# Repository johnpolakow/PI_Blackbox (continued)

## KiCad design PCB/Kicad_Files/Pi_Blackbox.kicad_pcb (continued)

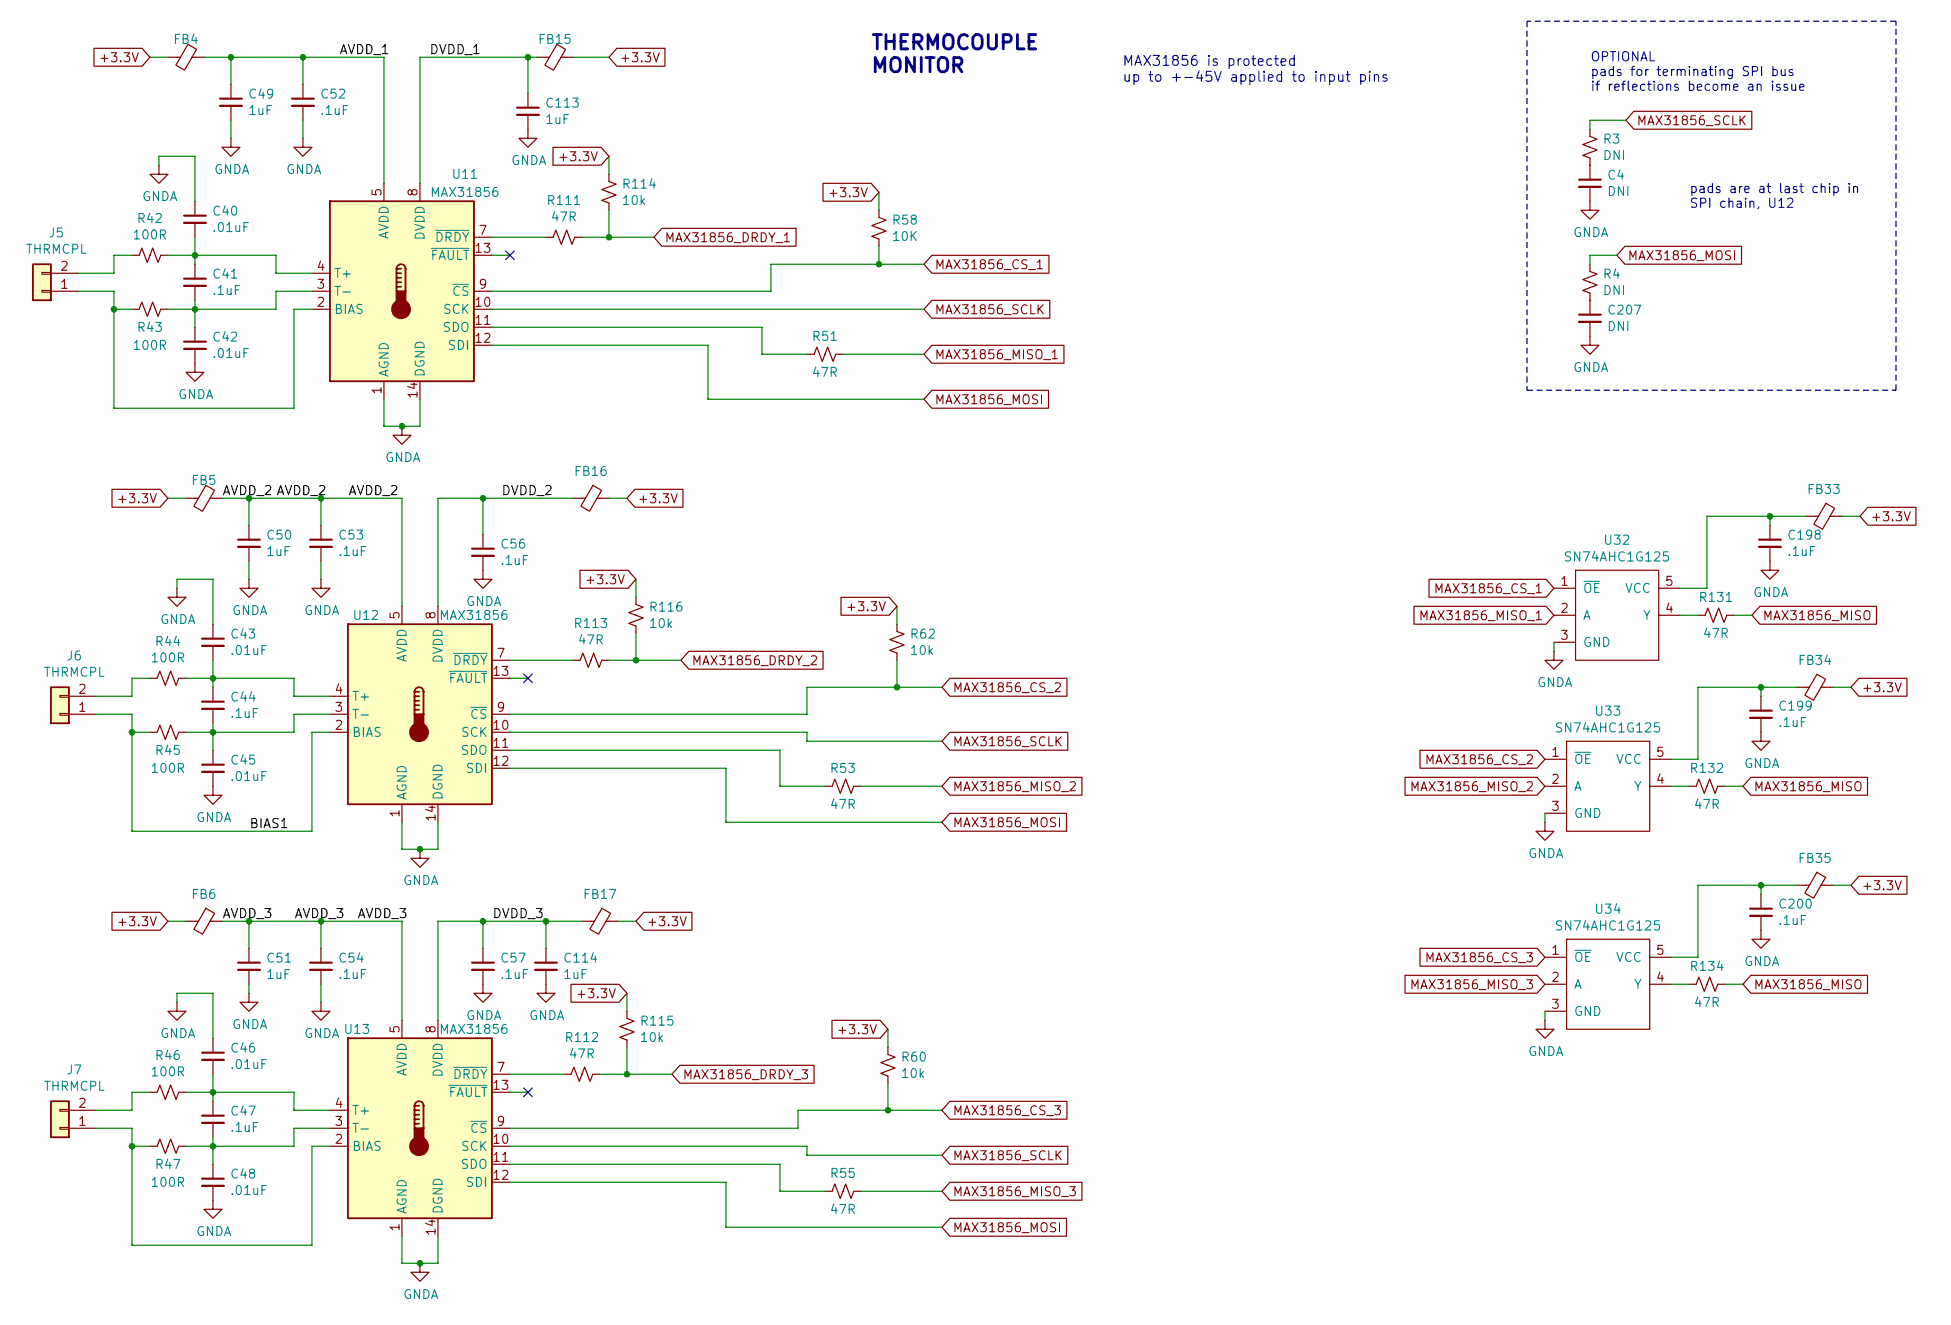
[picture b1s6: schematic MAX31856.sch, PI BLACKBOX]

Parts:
C4, C207: DNI; C_0603_1608Metric_Pad1.05x0.95mm_HandSolder
C40, C42, C43, C45, C46, C48: .01uF; C_0402_1005Metric
C41, C52, C53, C54, C56, C57: .1uF; C_0603_1608Metric_Pad1.05x0.95mm_HandSolder
C44, C47, C198, C199, C200: .1uF; C_0402_1005Metric
C49, C50, C51, C113, C114: 1uF; C_0603_1608Metric_Pad1.05x0.95mm_HandSolder
FB4, FB5, FB6, FB15, FB16, FB17: FB; R_0805_2012Metric_Pad1.15x1.40mm_HandSolder
FB33, FB34, FB35: FB; R_0402_1005Metric
J5, J6, J7: THRMCPL; Thermocouple_Connect
R3, R4: DNI; R_0603_1608Metric_Pad1.05x0.95mm_HandSolder
R42, R43, R44, R45, R46, R47: 100R; R_0402_1005Metric
R51, R53, R55, R111, R112, R113, R131, R132, R134: 47R; R_0402_1005Metric
R58: 10K; R_0402_1005Metric
R60, R62, R114, R115, R116: 10k; R_0402_1005Metric
U11, U12, U13: MAX31856; TSSOP-14_4.4x5mm_P0.65mm
U32, U33, U34: SN74AHC1G125; SOT-23-5_HandSoldering

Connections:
+3.3V: FB4.2, FB5.2, FB6.2, FB15.1, FB16.1, FB17.1, FB33.1, FB34.1, FB35.1, R58.1, R60.1, R62.1, R114.1, R115.1, R116.1; also elsewhere on the board
/MAX31856/AVDD_1: C49.1, C52.1, FB4.1, U11.5 (AVDD)
/MAX31856/AVDD_2: C50.1, C53.1, FB5.1, U12.5 (AVDD)
/MAX31856/AVDD_3: C51.1, C54.1, FB6.1, U13.5 (AVDD)
/MAX31856/BIAS1: J6.1, R45.2, U12.2 (BIAS)
/MAX31856/DVDD_1: C113.1, FB15.2, U11.8 (DVDD)
/MAX31856/DVDD_2: C56.1, FB16.2, U12.8 (DVDD)
/MAX31856/DVDD_3: C57.1, C114.1, FB17.2, U13.8 (DVDD)
DAC_MOSI: R4.1, U11.12 (SDI), U12.12 (SDI), U13.12 (SDI); also elsewhere on the board
DAC_SCLK: R3.1, U11.10 (SCK), U12.10 (SCK), U13.10 (SCK); also elsewhere on the board
GNDA: C4.2, C40.1, C42.2, C43.1, C45.2, C46.1, C48.2, C49.2, C50.2, C51.2, C52.2, C53.2, C54.2, C56.2, C57.2, C113.2, C114.2, C198.2, C199.2, C200.2, C207.2, U11.1 (AGND), U11.14 (DGND), U12.1 (AGND), U12.14 (DGND), U13.1 (AGND), U13.14 (DGND), U32.3 (GND), U33.3 (GND), U34.3 (GND); also elsewhere on the board
MAX31856_CS_1: R58.2, U11.9 (~CS), U32.1 (~OE); also elsewhere on the board
MAX31856_CS_2: R62.2, U12.9 (~CS), U33.1 (~OE); also elsewhere on the board
MAX31856_CS_3: R60.2, U13.9 (~CS), U34.1 (~OE); also elsewhere on the board
MAX31856_DRDY_1: R111.1, R114.2; also elsewhere on the board
MAX31856_DRDY_2: R113.1, R116.2; also elsewhere on the board
MAX31856_DRDY_3: R112.1, R115.2; also elsewhere on the board
MAX31856_MISO: R131.1, R132.1, R134.1; also elsewhere on the board
MAX31856_MISO_1: R51.1, U32.2 (A)
MAX31856_MISO_2: R53.1, U33.2 (A)
MAX31856_MISO_3: R55.1, U34.2 (A)
unnamed: C4.1, R3.2
unnamed: C40.2, C41.1, R42.1, U11.4 (T+)
unnamed: C41.2, C42.1, R43.1, U11.3 (T-)
unnamed: C43.2, C44.1, R44.1, U12.4 (T+)
unnamed: C44.2, C45.1, R45.1, U12.3 (T-)
unnamed: C46.2, C47.1, R46.1, U13.4 (T+)
unnamed: C47.2, C48.1, R47.1, U13.3 (T-)
unnamed: C198.1, FB33.2, U32.5 (VCC)
unnamed: C199.1, FB34.2, U33.5 (VCC)
unnamed: C200.1, FB35.2, U34.5 (VCC)
unnamed: C207.1, R4.2
unnamed: J5.1, R43.2, U11.2 (BIAS)
unnamed: J5.2, R42.2
unnamed: J6.2, R44.2
unnamed: J7.1, R47.2, U13.2 (BIAS)
unnamed: J7.2, R46.2
unnamed: R51.2, U11.11 (SDO)
unnamed: R53.2, U12.11 (SDO)
unnamed: R55.2, U13.11 (SDO)
unnamed: R111.2, U11.7 (~DRDY)
unnamed: R112.2, U13.7 (~DRDY)
unnamed: R113.2, U12.7 (~DRDY)
unnamed: R131.2, U32.4 (Y)
unnamed: R132.2, U33.4 (Y)
unnamed: R134.2, U34.4 (Y)

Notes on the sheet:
MAX31856 is protected up to +-45V applied to input pins
THERMOCOUPLE MONITOR
OPTIONAL pads for terminating SPI bus if reflections become an issue
pads are at last chip in SPI chain, U12

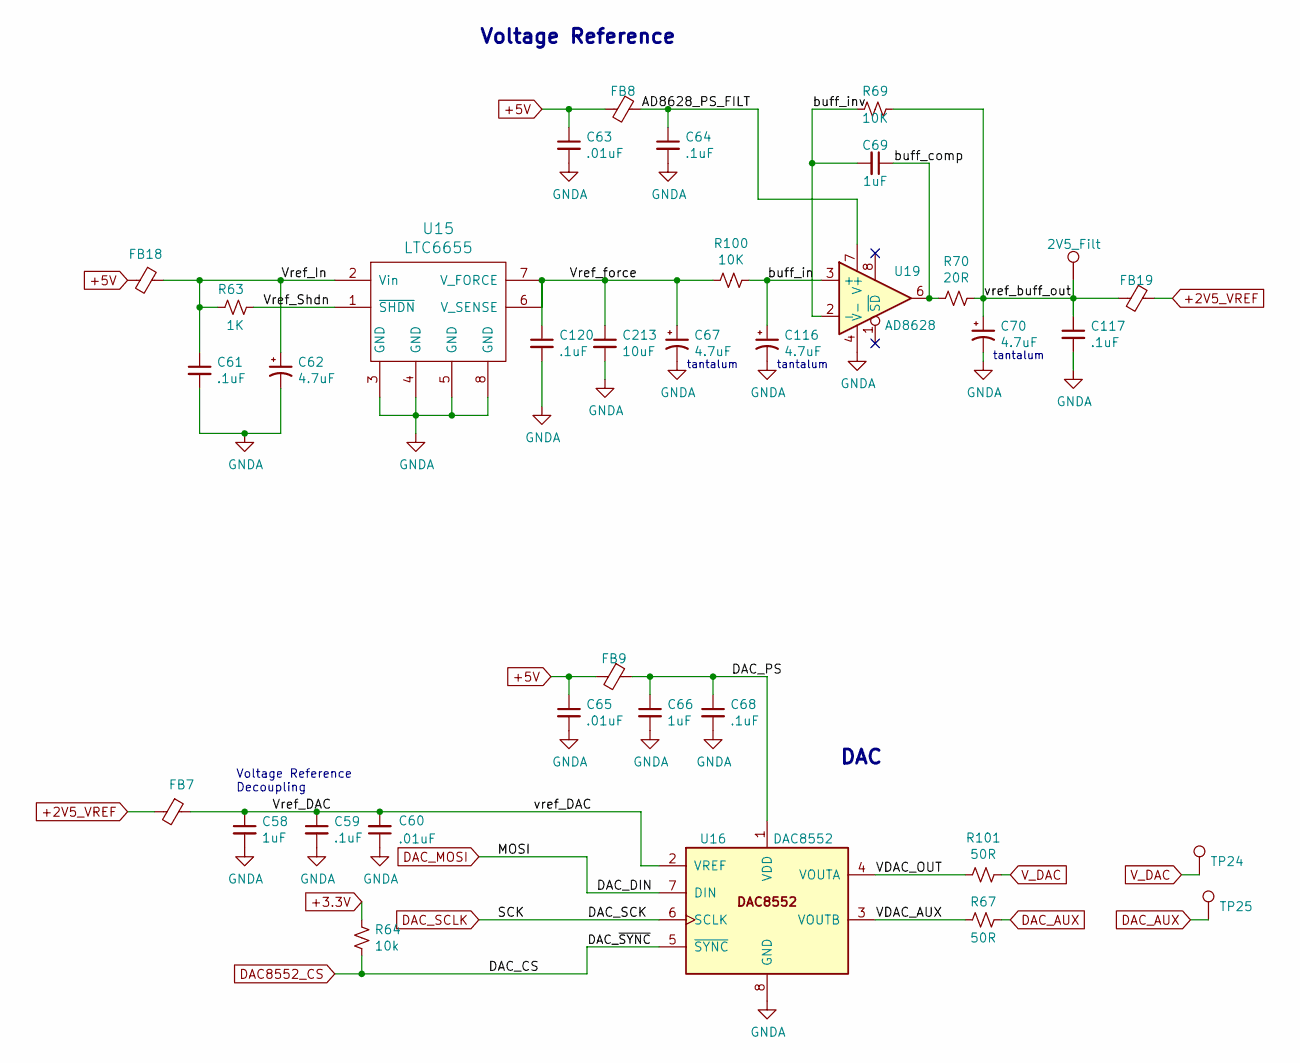
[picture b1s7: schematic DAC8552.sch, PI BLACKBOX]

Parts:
C58, C66, C69: 1uF; C_0805_2012Metric_Pad1.15x1.40mm_HandSolder
C59, C61, C64, C68, C117, C120: .1uF; C_0603_1608Metric_Pad1.05x0.95mm_HandSolder
C60, C63, C65: .01uF; C_0603_1608Metric_Pad1.05x0.95mm_HandSolder
C62, C67, C70, C116: 4.7uF; CP_EIA-3528-21_Kemet-B_Pad1.50x2.35mm_HandSolder
C213: 10uF; C_0805_2012Metric_Pad1.15x1.40mm_HandSolder
FB7, FB8, FB9, FB19: FB; R_0805_2012Metric_Pad1.15x1.40mm_HandSolder
FB18: FB; L_0805_2012Metric_Pad1.15x1.40mm_HandSolder
R63: 1K; R_0402_1005Metric
R64: 10k; R_0402_1005Metric
R67, R101: 50R; R_0402_1005Metric
R69: 10K; R_0603_1608Metric_Pad1.05x0.95mm_HandSolder
R70: 20R; R_0805_2012Metric_Pad1.15x1.40mm_HandSolder
R100: 10K; R_0402_1005Metric
TP23: 2V5_Filt; TestPoint_SMT_Keystone_5190
TP24: VDAC; TestPoint_SMT_Keystone_5190
TP25: DAC_AUX; TestPoint_Pad_D1.5mm
U15: LTC6655; LTC6655_LS8
U16: DAC8552; VSSOP-8_3.0x3.0mm_P0.65mm
U19: AD8628; SOIC-8_5.275x5.275mm_P1.27mm

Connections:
+2V5_VREF: FB7.2, FB19.1; also elsewhere on the board
+3.3V: R64.1; also elsewhere on the board
+5V: C63.1, C65.1, FB8.2, FB9.2, FB18.2; also elsewhere on the board
/DAC8552/AD8628_PS_FILT: C64.1, FB8.1, U19.7 (V+)
/DAC8552/DAC_PS: C66.1, C68.1, FB9.1, U16.1 (VDD)
/DAC8552/VDAC_AUX: R67.2, U16.3 (VOUTB)
/DAC8552/VDAC_OUT: R101.2, U16.4 (VOUTA)
/DAC8552/Vref_DAC: C58.1, C59.1, C60.2, FB7.1, U16.2 (VREF)
/DAC8552/Vref_In: C61.1, C62.1, FB18.1, R63.1, U15.2 (Vin)
/DAC8552/Vref_Shdn: R63.2, U15.1 (~SHDN)
/DAC8552/Vref_force: C67.1, C120.1, C213.1, R100.2, U15.6 (V_SENSE), U15.7 (V_FORCE)
/DAC8552/buff_comp: C69.1, R70.2, U19.6
/DAC8552/buff_in: C116.1, R100.1, U19.3 (+)
/DAC8552/buff_inv: C69.2, R69.2, U19.2 (-)
/DAC8552/vref_buff_out: C70.1, C117.1, FB19.2, R69.1, R70.1, TP23.1
DAC8552_CS: R64.2, U16.5 (~SYNC); also elsewhere on the board
DAC_AUX: R67.1, TP25.1
DAC_MOSI: U16.7 (DIN); also elsewhere on the board
DAC_SCLK: U16.6 (SCLK); also elsewhere on the board
GNDA: C58.2, C59.2, C60.1, C61.2, C62.2, C63.2, C64.2, C65.2, C66.2, C67.2, C68.2, C70.2, C116.2, C117.2, C120.2, C213.2, U15.3 (GND), U15.4 (GND), U15.5 (GND), U15.8 (GND), U16.8 (GND), U19.4 (V-); also elsewhere on the board
V_DAC: R101.1, TP24.1; also elsewhere on the board

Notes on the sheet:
Voltage Reference
DAC
Voltage Reference Decoupling
tantalum

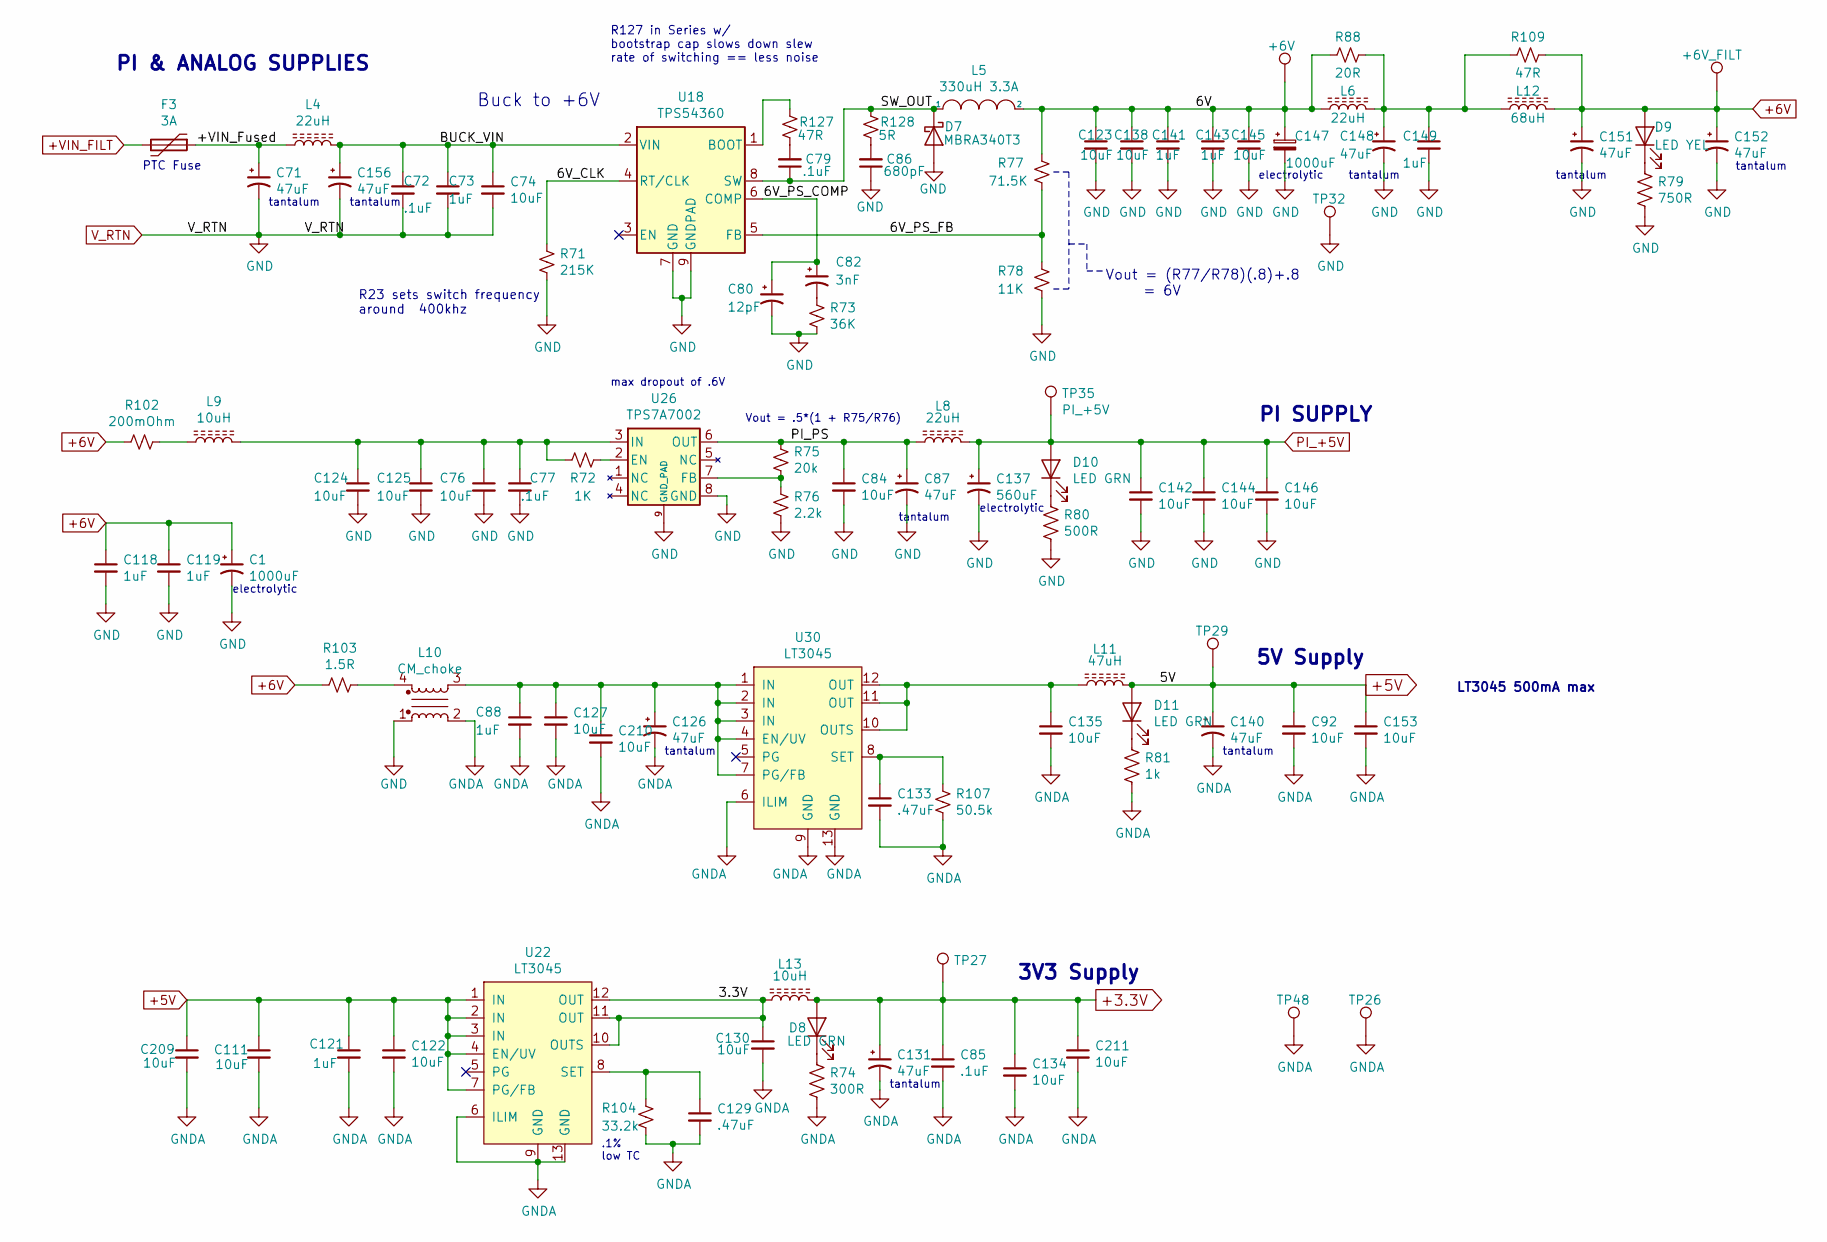
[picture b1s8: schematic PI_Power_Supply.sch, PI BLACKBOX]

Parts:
C1: 1000uF; CP_Radial_D12.5mm_P5.00mm; MFG Part # EEU-FR1V102B
C71, C87, C126, C131, C140, C148, C151, C152, C156: 47uF; T495X476K035ATE300
C72, C77: .1uF; C_0603_1608Metric_Pad1.05x0.95mm_HandSolder
C73, C88, C118, C119, C141, C143, C149: 1uF; C_0805_2012Metric_Pad1.15x1.40mm_HandSolder
C74, C76, C84, C92, C123, C124, C125, C127, C130, C134, C135, C138, C142, C144, C145, C146, C153: 10uF; C_1206_3216Metric_Pad1.42x1.75mm_HandSolder
C79: .1uF; C_0805_2012Metric_Pad1.15x1.40mm_HandSolder
C80: 12pF; C_0603_1608Metric_Pad1.05x0.95mm_HandSolder
C82: 3nF; C_0603_1608Metric_Pad1.05x0.95mm_HandSolder
C85: .1uF; R_0603_1608Metric_Pad1.05x0.95mm_HandSolder
C86: 680pF; C_0603_1608Metric_Pad1.05x0.95mm_HandSolder
C111, C122, C209, C210, C211: 10uF; C_0805_2012Metric_Pad1.15x1.40mm_HandSolder
C121: 1uF; C_0603_1608Metric_Pad1.05x0.95mm_HandSolder
C129, C133: .47uF; C_0402_1005Metric
C137: 560uF; CP_Radial_D10.0mm_P5.00mm
C147: 1000uF; CP_Radial_D12.5mm_P5.00mm
D7: MBRA340T3; MBRA430T
D8, D10, D11: LED GRN; LED_0805_2012Metric_Pad1.15x1.40mm_HandSolder
D9: LED YEL; LED_0805_2012Metric_Pad1.15x1.40mm_HandSolder
F3: 3A; Fuse_2920
L4: 22uH; L_Bourns_SRP1038
L5: 330uH 3.3A; Murata1433433C
L6, L8: 22uH; Sumida_CDRH105
L9: 10uH; 10uH_Wurth_74479887310A
L10: CM_choke; CM_Choke_EPCOS_B82720K
L11: 47uH; RLB9012-470KL
L12: 68uH; L_Wuerth_WE-PD
L13: 10uH; L_1210_3225Metric_Pad1.42x2.65mm_HandSolder
R71: 215K; R_0603_1608Metric_Pad1.05x0.95mm_HandSolder
R72: 1K; R_0402_1005Metric
R73: 36K; R_0603_1608Metric_Pad1.05x0.95mm_HandSolder
R74: 300R; R_0402_1005Metric
R75: 20k; R_0603_1608Metric_Pad1.05x0.95mm_HandSolder
R76: 2.2k; R_0603_1608Metric_Pad1.05x0.95mm_HandSolder
R77: 71.5K; R_0603_1608Metric_Pad1.05x0.95mm_HandSolder
R78: 11K; R_0603_1608Metric_Pad1.05x0.95mm_HandSolder
R79: 750R; R_0402_1005Metric
R80: 500R; R_0402_1005Metric
R81: 1k; R_0402_1005Metric
R88: 20R; R_1210_3225Metric_Pad1.42x2.65mm_HandSolder
R102: 200mOhm; R_1206_3216Metric_Pad1.42x1.75mm_HandSolder
R103: 1.5R; R_1206_3216Metric_Pad1.42x1.75mm_HandSolder
R104: 33.2k; R_0402_1005Metric
R107: 50.5k; R_0603_1608Metric_Pad1.05x0.95mm_HandSolder
R109: 47R; R_1210_3225Metric_Pad1.42x2.65mm_HandSolder
R127: 47R; R_0603_1608Metric_Pad1.05x0.95mm_HandSolder
R128: 5R; R_0805_2012Metric_Pad1.15x1.40mm_HandSolder
TP16: +6V_FILT; TestPoint_SMT_Keystone_5190
TP26, TP48: GNDA; TestPoint_SMT_Keystone_5190
TP27: +3V3; TestPoint_SMT_Keystone_5190
TP28: +6V; TestPoint_SMT_Keystone_5190
TP29: +5V_FILT; TestPoint_SMT_Keystone_5190
TP32: GND; TestPoint_SMT_Keystone_5190
TP35: PI_+5V; TestPoint_SMT_Keystone_5190
U18: TPS54360; Power_Pad_SO
U22, U30: LT3045; MSOP-12-1EP_3x4mm_P0.65mm_EP1.65x2.85mm_ThermalVias
U26: TPS7A7002; SOIC-8-1EP_3.9x4.9mm_P1.27mm_EP2.514x3.2mm_ThermalVias

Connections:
+3.3V: C85.1, C131.1, C134.1, C211.1, D8.2 (A), L13.2, TP27.1; also elsewhere on the board
+5V: C92.1, C111.1, C121.1, C122.1, C140.1, C153.1, C209.1, D11.2 (A), L11.2, TP29.1, U22.1 (IN), U22.2 (IN), U22.3 (IN), U22.4 (EN/UV), U22.7 (PG/FB); also elsewhere on the board
+6V: C1.1, C118.1, C119.1, C151.1, C152.1, D9.2 (A), L12.2, R102.2, R103.2, R109.1, TP16.1; also elsewhere on the board
+VIN_FILT: F3.2; also elsewhere on the board
/PI_Power_Supply/3.3V: C130.1, L13.1, U22.10 (OUTS), U22.11 (OUT), U22.12 (OUT)
/PI_Power_Supply/6V: C123.1, C138.1, C141.1, C143.1, C145.1, C147.1, L5.2, L6.1, R77.1, R88.2, TP28.1
/PI_Power_Supply/6V_CLK: R71.1, U18.4 (RT/CLK)
/PI_Power_Supply/6V_PS_COMP: C80.1, C82.1, U18.6 (COMP)
/PI_Power_Supply/6V_PS_FB: R77.2, R78.1, U18.5 (FB)
/PI_Power_Supply/+VIN_Fused: C71.1, F3.1, L4.1
/PI_Power_Supply/BUCK_VIN: C72.1, C73.1, C74.1, C156.1, L4.2, U18.2 (VIN)
/PI_Power_Supply/PI_PS: C84.1, C87.1, L8.1, R75.1, U26.6 (OUT)
/PI_Power_Supply/SW_OUT: C79.1, D7.1 (K), L5.1, R128.1, U18.8 (SW)
GND: C1.2, C71.2, C72.2, C73.2, C74.2, C76.2, C77.2, C80.2, C84.2, C86.1, C87.2, C118.2, C119.2, C123.2, C124.2, C125.2, C137.2, C138.2, C141.2, C142.2, C143.2, C144.2, C145.2, C146.2, C147.2, C148.2, C149.2, C151.2, C152.2, C156.2, D7.2 (A), L10.1, R71.2, R73.2, R76.2, R78.2, R79.2, R80.2, TP32.1, U18.7 (GND), U18.9 (GNDPAD), U26.8 (GND), U26.9 (GND_PAD); also elsewhere on the board
GNDA: C85.2, C88.2, C92.2, C111.2, C121.2, C122.2, C126.2, C127.2, C129.2, C130.2, C131.2, C133.2, C134.2, C135.2, C140.2, C153.2, C209.2, C210.2, C211.2, L10.2, R74.2, R81.2, R104.2, R107.2, TP26.1, TP48.1, U22.6 (ILIM), U22.9 (GND), U22.13 (GND), U30.6 (ILIM), U30.9 (GND), U30.13 (GND); also elsewhere on the board
unnamed: C79.2, R127.2
unnamed: C82.2, R73.1
unnamed: C86.2, R128.2
unnamed: C76.1, C77.1, C124.1, C125.1, L9.2, R72.2, U26.3 (IN)
unnamed: C88.1, C126.1, C127.1, C210.1, L10.3, U30.1 (IN), U30.2 (IN), U30.3 (IN), U30.4 (EN/UV), U30.7 (PG/FB)
unnamed: C129.1, R104.1, U22.8 (SET)
unnamed: C133.1, R107.1, U30.8 (SET)
unnamed: C135.1, L11.1, U30.10 (OUTS), U30.11 (OUT), U30.12 (OUT)
unnamed: C148.1, C149.1, L6.2, L12.1, R88.1, R109.2
unnamed: D8.1 (K), R74.1
unnamed: D9.1 (K), R79.1
unnamed: D10.1 (K), R80.1
unnamed: D11.1 (K), R81.1
unnamed: L9.1, R102.1
unnamed: L10.4, R103.1
unnamed: R72.1, U26.2 (EN)
unnamed: R75.2, R76.1, U26.7 (FB)
unnamed: R127.1, U18.1 (BOOT)
PI_+5V: C137.1, C142.1, C144.1, C146.1, D10.2 (A), L8.2, TP35.1; also elsewhere on the board

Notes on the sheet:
Vout = (R77/R78)(.8)+.8 = 6V
R23 sets switch frequency around 400khz
3V3 Supply
Buck to +6V
PTC Fuse
PI & ANALOG SUPPLIES
Vout = .5*(1 + R75/R76)
PI SUPPLY
tantalum
max dropout of .6V
.1% low TC
electrolytic
R127 in Series w/ bootstrap cap slows down slew rate of switching == less noise
LT3045 500mA max
5V Supply

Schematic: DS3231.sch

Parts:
BT1: Battery_Holder; BatteryHolder_Keystone_1058_2032; MFG Part # 1058
C160, C168: 0.1uF; C_0603_1608Metric_Pad1.05x0.95mm_HandSolder
FB26: ferrite; R_0603_1608Metric_Pad1.05x0.95mm_HandSolder
R121, R122: 22R; R_0402_1005Metric
R123, R124: 2k; R_0402_1005Metric
R125, R126: 10k; R_0402_1005Metric
U29: DS3231MZ+; SOIC-8_W3.9mm; MPN DS3231MZ/V+; Digi-Key_PN DS3231MZ/V+-ND

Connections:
+3.3V: FB26.2, R123.1, R124.1, R125.1, R126.1; also elsewhere on the board
GNDA: BT1.2 (-), C160.2, C168.2, U29.5 (GND); also elsewhere on the board
unnamed: C160.1, FB26.1, U29.2 (VCC)
unnamed: R121.1, R124.2, U29.7 (SDA)
unnamed: R122.1, R123.2, U29.8 (SCL)
unnamed: R125.2, U29.3 (~INT~/SQW)
unnamed: R126.2, U29.1 (32KHZ)
PI_SCL: R122.2; also elsewhere on the board
PI_SDA: R121.2; also elsewhere on the board
VBat: BT1.1 (+), C168.1, U29.6 (VBAT); also elsewhere on the board

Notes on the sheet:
REAL TIME CLOCK DS3231

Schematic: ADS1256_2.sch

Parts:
C181: 4.7uF; CP_EIA-3528-21_Kemet-B_Pad1.50x2.35mm_HandSolder
C182, C184, C208: 1uF; C_0603_1608Metric_Pad1.05x0.95mm_HandSolder
C183, C186, C188, C190, C191: .1uF; C_0603_1608Metric_Pad1.05x0.95mm_HandSolder
C185: .1uF; C_0805_2012Metric_Pad1.15x1.40mm_HandSolder
C187, C189: 1uF; R_0603_1608Metric_Pad1.05x0.95mm_HandSolder
C192, C193: 20pF; C_0603_1608Metric_Pad1.05x0.95mm_HandSolder
L16, L17: 10uH; MLZ2012N100LT000
R130, R138: 2k; R_0402_1005Metric
R133: 10k; R_0402_1005Metric
R136, R137: 47R; R_0402_1005Metric
U31: ADS1256; SSOP-28_5.3x10.2mm_P0.65mm
Y2: 7.68 Mhz; Crystal_SMD_TXC

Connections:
+2V5_VREF: C181.1, C182.1, C183.1, U31.4 (VREFP); also elsewhere on the board
+3.3V: C184.1, L16.1, R130.1, R133.1, R138.1; also elsewhere on the board
+5V: C186.1, L17.1; also elsewhere on the board
/ADS1256_2/ADS2_AVDD: C188.1, C189.1, C191.1, L17.2, U31.1 (AVDD)
/ADS1256_2/ADS2_DRDY2: R136.2, U31.21 (~DRDY)
/ADS1256_2/ADS2_DVDD: C187.1, C190.1, L16.2, U31.16 (DVDD)
/ADS1256_2/ADS2_MISO2: R137.2, U31.22 (DOUT)
ADS1256_MISO: R137.1; also elsewhere on the board
ADS1256_MOSI: U31.23 (DIN); also elsewhere on the board
ADS1256_SCLK: U31.24 (SCLK); also elsewhere on the board
COOL_PWR_I: C208.1, U31.6 (AIN0); also elsewhere on the board
CRYSTALA: C192.1, U31.19 (XTAL1/CLKIN), Y2.2
CRYSTALB: C193.1, U31.18 (XTAL2), Y2.1
GNDA: C181.2, C182.2, C183.2, C184.2, C186.2, C187.2, C188.2, C189.2, C190.2, C191.2, C192.2, C193.2, C208.2, U31.2 (AGND), U31.3 (VREFN), U31.5 (AINCOM), U31.7 (AIN1), U31.11 (AIN5), U31.13 (AIN7), U31.17 (DGND); also elsewhere on the board
HEAT_LOAD_I: U31.10 (AIN4); also elsewhere on the board
HEAT_LOAD_V: U31.12 (AIN6); also elsewhere on the board
TEMP_DIODE: C185.1, U31.8 (AIN2); also elsewhere on the board
TEMP_DIODE_RTN: C185.2, U31.9 (AIN3); also elsewhere on the board
~ADS1256_CS_1: R130.2, U31.20 (~CS); also elsewhere on the board
~ADS1256_RESET: R133.2, U31.15 (~RESET); also elsewhere on the board
~ADS1265_DRDY2: R136.1, R138.2; also elsewhere on the board

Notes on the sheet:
ADC
Analog Inputs

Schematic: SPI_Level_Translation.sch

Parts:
C201, C202, C203, C204, C205, C206: 0.1uF; C_0603_1608Metric_Pad1.05x0.95mm_HandSolder
R5, R6, R7, R147: 10k; R_0402_1005Metric
R135, R139, R140, R141, R142, R143, R144, R145, R146: 47R; R_0402_1005Metric
TP5: MISO_1; TestPoint_SMT_Keystone_5190
TP7: MOSI_1; TestPoint_SMT_Keystone_5190
TP8: SCLK_0; TestPoint_SMT_Keystone_5190
TP9: SCLK_1; TestPoint_SMT_Keystone_5190
TP10: MOSI_0; TestPoint_SMT_Keystone_5190
TP11: GND; TestPoint_SMT_Keystone_5190
TP12: MISO_0; TestPoint_SMT_Keystone_5190
TP50: PI_SCLK_0; TestPoint_SMT_Keystone_5190
U35, U36, U37: SN74HC125; SN74LVC125APWR; MPN SN74HC125A; Digi-Key_PN 296-1222-1-ND

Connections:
+3.3V: C201.1, C202.1, C203.1, C204.1, C205.1, C206.1, R5.1, R6.1, R7.1, R147.1, U35.14 (VCC), U36.14 (VCC), U37.14 (VCC); also elsewhere on the board
ADS1256_MISO: TP12.1, U35.12 (4A); also elsewhere on the board
ADS1256_MOSI: R142.1, TP10.1; also elsewhere on the board
ADS1256_SCLK: R141.1, TP8.1; also elsewhere on the board
DAC_MOSI: R144.1, R146.1; also elsewhere on the board
DAC_SCLK: R143.1, R145.1; also elsewhere on the board
GND: C201.2, C202.2, C203.2, C204.2, C205.2, C206.2, TP11.1, U35.7 (GND), U36.7 (GND), U37.7 (GND); also elsewhere on the board
MAX31856_MISO: U36.12 (4A), U37.12 (4A); also elsewhere on the board
unnamed: R135.1, U35.11 (4Y)
unnamed: R139.1, U36.11 (4Y)
unnamed: R140.1, TP5.1, U37.11 (4Y)
unnamed: R141.2, U35.3 (1Y)
unnamed: R142.2, U35.6 (2Y)
unnamed: R143.2, U36.3 (1Y)
unnamed: R144.2, U36.6 (2Y)
unnamed: R145.2, U37.3 (1Y)
unnamed: R146.2, U37.6 (2Y)
PI_MISO_0: R135.2, R139.2; also elsewhere on the board
PI_MISO_1: R140.2; also elsewhere on the board
PI_MOSI_0: U35.5 (2A), U36.5 (2A); also elsewhere on the board
PI_MOSI_1: TP7.1, U37.5 (2A); also elsewhere on the board
PI_SCLK_0: TP50.1, U35.2 (1A), U36.2 (1A); also elsewhere on the board
PI_SCLK_1: TP9.1, U37.2 (1A); also elsewhere on the board
~BUF_EN_0: R7.2, R147.2, U35.1 (~1OE), U35.4 (~2OE), U35.13 (~4OE); also elsewhere on the board
~BUF_EN_1: R5.2, U36.1 (~1OE), U36.4 (~2OE), U36.13 (~4OE); also elsewhere on the board
~BUF_EN_2: R6.2, U37.1 (~1OE), U37.4 (~2OE), U37.13 (~4OE); also elsewhere on the board

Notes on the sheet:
turn on when ads1 or ads2 CS goes low

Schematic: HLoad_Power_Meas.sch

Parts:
C13: 1.5uF; C_1210_3225Metric_Pad1.42x2.65mm_HandSolder
C157, C158: 0.1uF; C_0603_1608Metric_Pad1.05x0.95mm_HandSolder
C161: 1uF; C_0603_1608Metric_Pad1.05x0.95mm_HandSolder
C162: .1uF; C_0402_1005Metric
C163, C164, C167: 1uF; C_1210_3225Metric_Pad1.42x2.65mm_HandSolder
C165: 10uF; C_0805_2012Metric_Pad1.15x1.40mm_HandSolder
C166: .1uF; C_0603_1608Metric_Pad1.05x0.95mm_HandSolder
FB11, FB21, FB22, FB23: FB; R_0603_1608Metric_Pad1.05x0.95mm_HandSolder
R15: 1 kΩ; R_0402_1005Metric
R16: 1KΩ; R_0402_1005Metric
R17: 100 Ω; R_0402_1005Metric
R18: 1KΩ; R_0603_1608Metric_Pad1.05x0.95mm_HandSolder
R83: 100 Ω; R_0603_1608Metric_Pad1.05x0.95mm_HandSolder
TP34, TP36: test_pad; Probe_Test_Pad
U4: AD8278; SOIC-8_5.23x5.23mm_P1.27mm
U5: LT5400; MSOP-8_3x3mm_P0.65mm
U25: AD8417; SOIC-8_3.9x4.9mm_P1.27mm
U27, U28: AD8628; SOIC-8_3.9x4.9mm_P1.27mm
VLoad/4, VLoad/8: Jumper; SolderJumper-2_P1.3mm_Open_RoundedPad1.0x1.5mm

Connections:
+5V: FB21.1, FB22.1, FB23.1; also elsewhere on the board
/Heat_Load/HLoad: U25.8 (IN+); also elsewhere on the board
/Heat_Load/HLoad_Power_Meas/GUARD: C165.2, R18.2, U28.2 (-)
/Heat_Load/HLoad_Power_Meas/GUARD2: C161.2, R16.2, U27.2 (-)
/Heat_Load/HLoad_Power_Meas/I_Load: R15.2, U25.5 (OUT)
/Heat_Load/HLoad_Power_Meas/VLoad_div2: U4.5, U4.6, U5.1 (R1_in)
/Heat_Load/HLoad_Power_Meas/V_div4: TP34.1, U5.2 (R2_in), U5.3 (R3_in), VLoad/4.1
/Heat_Load/HLoad_Power_Meas/V_div8: TP36.1, U5.5 (R4_out), U5.6 (R3_out), VLoad/8.1
GND: C13.1, U4.2, U4.4 (V-); also elsewhere on the board
GNDA: C157.2, C158.2, C162.2, C163.2, C164.2, C166.2, C167.2, U4.1, U5.4 (R4_in), U25.2 (GND), U25.3 (REF2), U25.7 (REF1), U27.4 (V-), U28.4 (V-); also elsewhere on the board
HEAT_LOAD_I: C164.1, R16.1, R17.1; also elsewhere on the board
HEAT_LOAD_P: C13.2, U4.3, U25.1 (IN-); also elsewhere on the board
HEAT_LOAD_V: C167.1, R18.1, R83.1; also elsewhere on the board
LOAD_PS: FB11.1; also elsewhere on the board
unnamed: C157.1, FB11.2, U4.7 (V+)
unnamed: C158.1, FB21.2, U25.6 (VS)
unnamed: C161.1, R17.2, U27.6
unnamed: C162.1, FB22.2, U27.7 (V+)
unnamed: C163.1, U28.3 (+), VLoad/4.2, VLoad/8.2
unnamed: C165.1, R83.2, U28.6
unnamed: C166.1, FB23.2, U28.7 (V+)
unnamed: R15.1, U27.3 (+)
unnamed: U5.7 (R2_out), U5.8 (R1_out)

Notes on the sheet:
FILM
AD8278 Difference Amp in divide by 2 config
LT5400 divides by 4
AD8417 has a Gain of 60
FILM
Total Division Ratio is 8. Max Input Voltage is around 17 V, so output is scaled to 2.125 VMax, which is within ADC reference voltage of 2.5V

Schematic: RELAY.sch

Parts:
C28: 560uF; CP_Radial_D10.0mm_P5.00mm
C95: 47uF; T495X476K035ATE300
C102: .1uF; C_0603_1608Metric_Pad1.05x0.95mm_HandSolder
C103, C112: 1uF; C_0805_2012Metric_Pad1.15x1.40mm_HandSolder
C110: 1000uF; CP_Radial_D12.5mm_P5.00mm
D1, D3: 1N5819; SOD123
D4: 1N4148; SOD123
D12: 1N4148W; SOD123
D13: LED GRN; LED_0805_2012Metric_Pad1.15x1.40mm_HandSolder
D15: LED GREEN; LED_0805_2012Metric_Pad1.15x1.40mm_HandSolder
D17: LED RED; LED_0805_2012Metric_Pad1.15x1.40mm_HandSolder
JP1, JP2, JP3, JP4: Jumper_NO; SolderJumper-2_P1.3mm_Open_RoundedPad1.0x1.5mm
K1: DSP1-L2-DC5V; Panasonic_DSP1-L2-DC5V-F
Q3: BCM856DS; SOT-23-6_Handsoldering
Q4, Q7: MMBT2222A; SOT-23_Handsoldering
Q5: DMG6602
Q6: IRML6401; SOT-23_Handsoldering
R30, R32, R33: 50KΩ; R_0603_1608Metric_Pad1.05x0.95mm_HandSolder
R82: 750Ω; R_0603_1608Metric_Pad1.05x0.95mm_HandSolder
R85, R86: 500Ω; R_0402_1005Metric
R87, R98, R99: 1KΩ; R_0402_1005Metric
R96, R97: 47KΩ; R_0603_1608Metric_Pad1.05x0.95mm_HandSolder

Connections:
+5V: Q3.1 (E), Q6.3 (D); also elsewhere on the board
+5V_RELAY_PS: C110.1, D4.1 (K), D12.1 (K), D15.2 (A), K1.1, K1.2, Q3.4 (E), Q6.2 (S)
+12V_REG: D1.2 (A), K1.8, K1.9, R30.1, R32.1; also elsewhere on the board
/Power_Input/Power_Measure/RELAY_ON: C95.1, C102.1, C103.1, D13.2 (A), K1.5; also elsewhere on the board
/Power_Input/RELAY/COOLER_OFF: C112.1, D17.2 (A), K1.12
COIL_A: D4.2 (A), JP1.1, JP1.2, JP2.1, JP3.1, K1.16, Q4.3 (C)
COIL_B: D12.2 (A), JP2.2, JP3.2, JP4.1, JP4.2, K1.15, Q7.3 (C)
GND: C95.2, C102.2, C103.2, C112.2, R87.2, R99.2; also elsewhere on the board
GNDA: C28.2, C110.2, Q4.2 (E), Q5.5 (S), Q7.2 (E), R33.2, R96.2, R97.2, R98.2; also elsewhere on the board
unnamed: C28.1, D1.1 (K), Q5.2 (S), R30.2
unnamed: D3.1 (K), R82.2
unnamed: D3.2 (A), Q5.1 (G), Q5.4 (D), R33.1
unnamed: D13.1 (K), R87.1
unnamed: D15.1 (K), R98.1
unnamed: D17.1 (K), R99.1
unnamed: Q3.2 (B), Q3.5 (B), Q3.6 (C), R96.1
unnamed: Q3.3 (C), Q6.1 (G), R97.1
unnamed: Q4.1 (B), R82.1, R85.2
unnamed: Q5.3 (G), Q5.6 (D), R32.2
unnamed: Q7.1 (B), R86.1
RELAY_RESET: R86.2; also elsewhere on the board
RELAY_SET: R85.1; also elsewhere on the board

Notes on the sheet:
nominal coil current is 60 mA
RELAY_OFF
Automatically shuts off relay at power off
Supply for relay reset circuit
IDEAL DIODE (SUPPLY TO TURN OFF RELAY)
RELAY_ON
RELAY OFF INDICATOR
ON INDICATOR

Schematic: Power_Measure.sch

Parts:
C99, C115: .1uF; C_0603_1608Metric_Pad1.05x0.95mm_HandSolder
C100, C101, C107, C214: 10uF; C_1206_3216Metric_Pad1.42x1.75mm_HandSolder
C128, C174, C175, C176, C179: 1uF; C_0805_2012Metric_Pad1.15x1.40mm_HandSolder
C136: 47uF; T495X476K035ATE300
C139, C150: 100uF; C_1210_3225Metric_Pad1.42x2.65mm_HandSolder
C169: 3.3uF; C_Rect_L7.2mm_W5.5mm_P5.00mm_FKS2_FKP2_MKS2_MKP2
C170: 1uF; C_1210_3225Metric_Pad1.42x2.65mm_HandSolder
C171, C172, C173: 0.1uF; C_0603_1608Metric_Pad1.05x0.95mm_HandSolder
C177: 1000pF; C_0402_1005Metric
C180: 4.7uF; CP_EIA-3528-21_Kemet-B_Pad1.50x2.35mm_HandSolder
D5: LED_GRN; LED_0805_2012Metric_Pad1.15x1.40mm_HandSolder
FB24: FB; R_0805_2012Metric_Pad1.15x1.40mm_HandSolder
FB25, FB28: Ferrite; R_0805_2012Metric_Pad1.15x1.40mm_HandSolder
FB30: ferrite; R_0805_2012Metric_Pad1.15x1.40mm_HandSolder
FB31: FB; L_0603_1608Metric_Pad1.05x0.95mm_HandSolder
FB32: ferrite; L_1210_3225Metric_Pad1.42x2.65mm_HandSolder
R20: 500; R_0603_1608Metric_Pad1.05x0.95mm_HandSolder
R94: 56 mΩ; R_1206_3216Metric_Pad1.42x1.75mm_HandSolder
R106: 1M; R_0603_1608Metric_Pad1.05x0.95mm_HandSolder
R108: 4.7k; R_0402_1005Metric
R117: 1.87k; R_0603_1608Metric_Pad1.05x0.95mm_HandSolder
R119: 100R; R_0603_1608Metric_Pad1.05x0.95mm_HandSolder
R120: 1M; C_0603_1608Metric_Pad1.05x0.95mm_HandSolder
R129: .1R; R_0603_1608Metric_Pad1.05x0.95mm_HandSolder
SCALE1: 500R; Potentiometer_Bourns_3214W_Vertical
TP44: -5V; TestPoint_SMT_Keystone_5190
TP45: Current_SNS; TestPoint_SMT_Keystone_5190
TP46: AD637_RMS; TestPoint_SMT_Keystone_5190
TP47: RMS_FILT; TestPoint_SMT_Keystone_5190
U8: AD8417; SOIC-8_3.9x4.9mm_P1.27mm
U21: AD8628; SOIC-8_3.9x4.9mm_P1.27mm
U23: LT1054L; SOIC-8_5.275x5.275mm_P1.27mm
U24: AD637; SOIC-16W_7.5x10.3mm_P1.27mm
ZERO1: 50K POT; Potentiometer_Bourns_3214W_Vertical

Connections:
+5V: FB24.1, FB25.1, FB28.1, FB31.1, R108.2, ZERO1.1; also elsewhere on the board
-5V: C179.1, C180.1, C214.1, D5.1 (K), FB30.1, R129.1, TP44.1, ZERO1.3
/Power_Input/Power_Measure/RELAY_ON: R94.2, U8.8 (+); also elsewhere on the board
/Power_Input/Power_Measure/RMS_OUT: C169.1, C170.1, R117.2, SCALE1.1, SCALE1.2, TP46.1, U24.11 (RMS_OUT)
COOLER_PWR: R94.1, U8.1 (-); also elsewhere on the board
COOL_PWR_I: R119.1, U21.2 (-); also elsewhere on the board
Current_Sns_Amp: TP45.1, U8.5, U24.15 (VIN)
GNDA: C99.2, C100.2, C101.2, C107.2, C115.2, C128.2, C136.2, C150.2, C172.2, C173.2, C174.2, C175.2, C176.2, C177.2, C179.2, C180.2, C214.2, R20.2, R120.2, U8.2 (GND), U8.3 (REF2), U8.4 (GND), U8.7 (REF1), U21.4 (V-), U23.3 (GND), U24.1 (BUF_IN), U24.3 (COM); also elsewhere on the board
unnamed: C99.1, FB24.2, U8.6 (V+)
unnamed: C100.1, C101.1, C107.1, C176.1, R117.1, R120.1, TP47.1, U21.3 (+)
unnamed: C115.1, FB25.2, U21.7 (V+)
unnamed: C128.1, C136.1, FB31.2, U23.8 (V+)
unnamed: C139.1, U23.2 (CAP+)
unnamed: C139.2, U23.4 (CAP-)
unnamed: C150.1, FB32.1, U23.5 (-VOUT)
unnamed: C169.2, C170.2, U24.10 (C_AVG)
unnamed: C171.1, C172.1, C174.1, FB28.2, U24.13 (+VS)
unnamed: C171.2, C173.1, C175.1, FB30.2, U24.12 (-VS)
unnamed: C177.1, R106.2, ZERO1.2
unnamed: D5.2 (A), R20.1
unnamed: FB32.2, R129.2
unnamed: R106.1, U24.4 (OFFSET)
unnamed: R108.1, U24.5 (CS)
unnamed: R119.2, U21.6
unnamed: SCALE1.3, U24.6 (DENOM)

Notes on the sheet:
TO ADS1256
RMS CURRENT
AD8628 is low noise, low offset autozero amp to provide low impedance source to ADC
20-25 turn trim pot
FILM
